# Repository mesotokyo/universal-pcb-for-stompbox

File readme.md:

# Universal PCB for Stompbox schematic and PCB for KiCAD

(Japanese version is [here](readme_ja.md) / 日本語版は[こちら](readme_ja.md))

## What is this?

KiCAD files to build Universal PCB for Stompbox. These files are created with KiCad 6.0.

## Notice

This schematic and PCB file need a `ak_misc` footprint library in [mst-kicad-lib](https://github.com/mesotokyo/mst-kicad-lib). 

## DISCLAIMER

FILES IN THIS REPOSITORY ARE PROVIDED "AS IS", WITHOUT WARRANTY OF ANY KIND, EXPRESS OR IMPLIED, INCLUDING BUT NOT LIMITED TO THE WARRANTIES OF MERCHANTABILITY, FITNESS FOR A PARTICULAR PURPOSE AND NONINFRINGEMENT. IN NO EVENT SHALL THE AUTHORS OR COPYRIGHT HOLDERS BE LIABLE FOR ANY CLAIM, DAMAGES OR OTHER LIABILITY, WHETHER IN AN ACTION OF CONTRACT, TORT OR OTHERWISE, ARISING FROM, OUT OF OR IN CONNECTION WITH IN FILES IN THIS REPOSITORY OR THE USE OR OTHER DEALINGS IN FILES IN THIS REPOSITORY.

## License

CC BY 4.0. For more information, please check https://creativecommons.org/licenses/by/4.0/ .

## Author

MST/mesotokyo

 - https://meso.tokyo/
 - https://x.com/mesotokyox

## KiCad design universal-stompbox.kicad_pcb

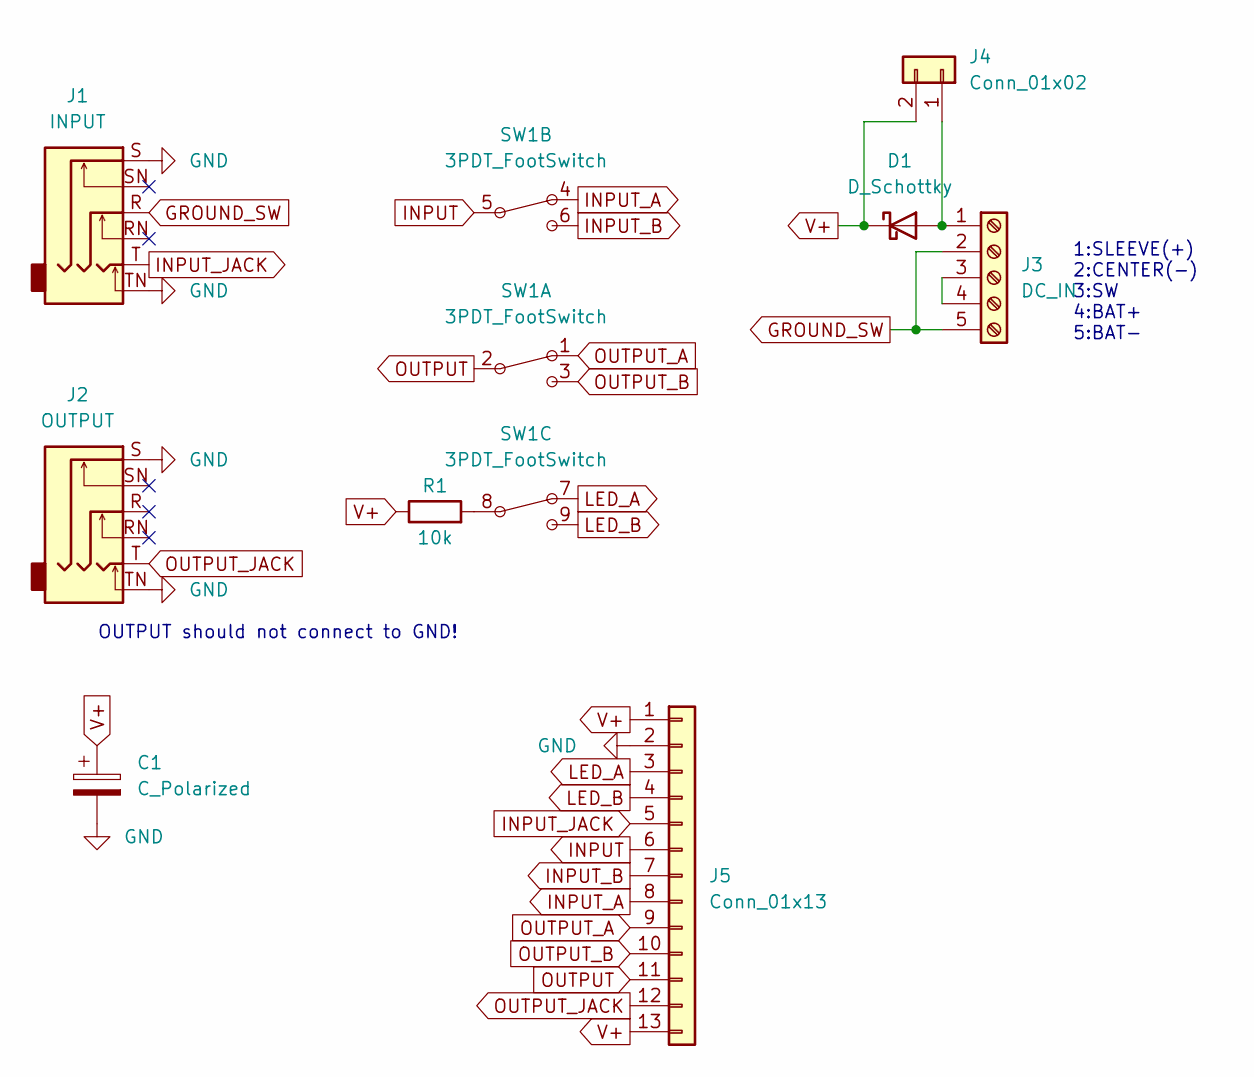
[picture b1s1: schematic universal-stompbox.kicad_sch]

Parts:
C1: C_Polarized; CP_Radial_D8.0mm_P3.50mm
D1: D_Schottky; D_DO-35_SOD27_P2.54mm_Vertical_AnodeUp
J1: INPUT; Jack_6.35mm_Neutrik_NMJ6HCD2_Horizontal
J2: OUTPUT; Jack_6.35mm_Neutrik_NMJ6HCD2_Horizontal
J3: DC_IN; TerminalBlock_TE_282834-5_1x05_P2.54mm_Horizontal
J4: Conn_01x02; PinSocket_1x02_P2.54mm_Vertical
J5: Conn_01x13; PinSocket_1x13_P2.54mm_Vertical
R1: 10k; R_Axial_DIN0204_L3.6mm_D1.6mm_P2.54mm_Vertical
SW1: 3PDT_FootSwitch

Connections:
GND: C1.2, J1.S, J1.TN, J2.S, J2.TN, J5.2
GROUND_SW: J1.R, J3.2, J3.5
INPUT: J5.6, SW1.5
INPUT_A: J5.8, SW1.4
INPUT_B: J5.7, SW1.6
INPUT_JACK: J1.T, J5.5
LED_A: J5.3, SW1.7
LED_B: J5.4, SW1.9
unnamed: D1.2 (A), J3.1, J4.1
unnamed: J3.3, J3.4
unnamed: R1.2, SW1.8
OUTPUT: J5.11, SW1.2
OUTPUT_A: J5.9, SW1.1
OUTPUT_B: J5.10, SW1.3
OUTPUT_JACK: J2.T, J5.12
V+: C1.1, D1.1 (K), J4.2, J5.1, J5.13, R1.1

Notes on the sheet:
1:SLEEVE(+) 2:CENTER(-) 3:SW 4:BAT+ 5:BAT-
OUTPUT should not connect to GND!

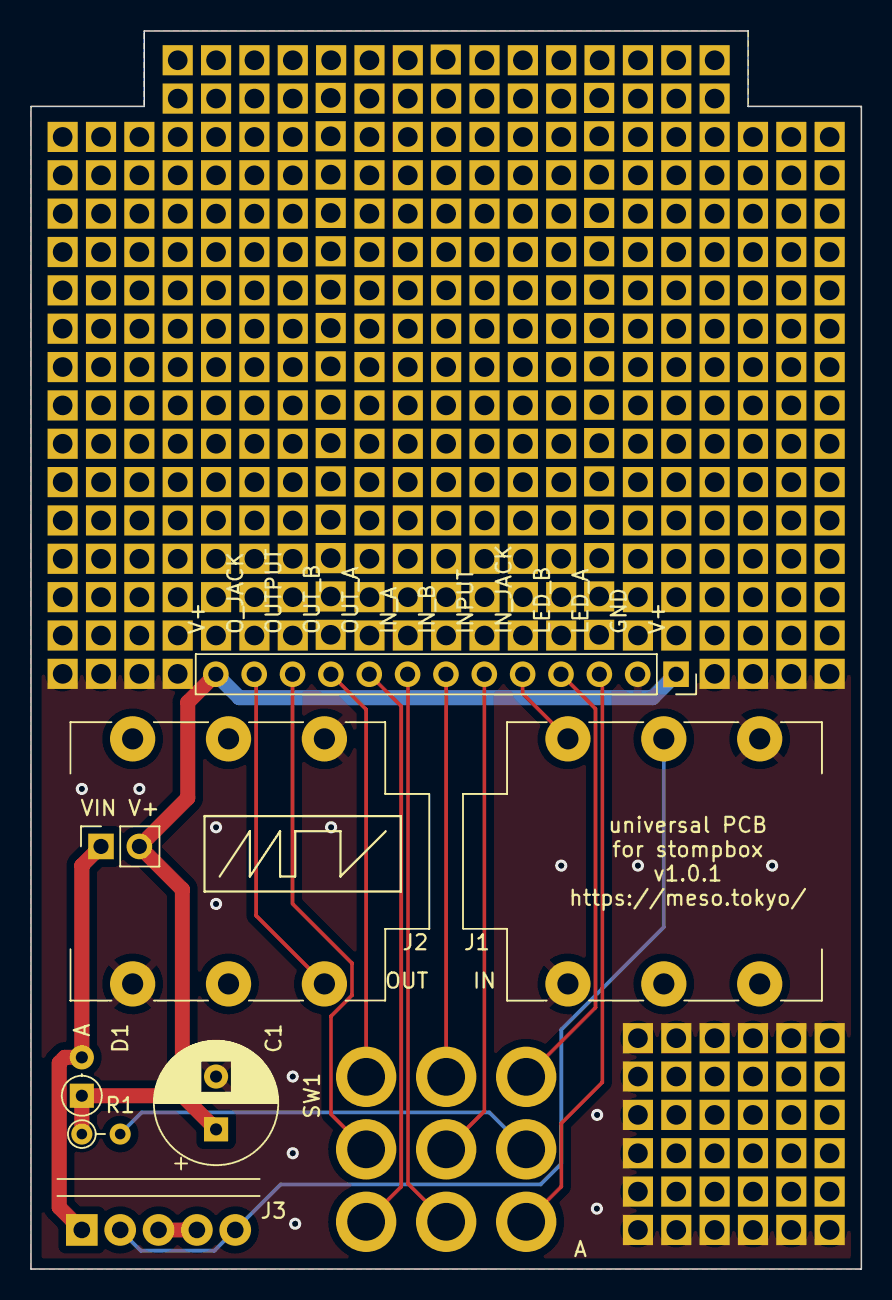
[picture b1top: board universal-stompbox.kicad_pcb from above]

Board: 2 copper layers, 55.0 x 82.0 mm, 9 parts (0 on the bottom side), 16 nets.
